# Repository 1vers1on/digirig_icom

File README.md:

# ICOM IC-2730 Digital Controller

A custom hardware controller for the ICOM IC-2730 radio, featuring digital audio processing and USB connectivity.

## Overview

This project provides a digital interface for the ICOM IC-2730 radio using a Raspberry Pi RP2350 microcontroller and TLV320AIC3204 audio codec. It handles both transmit and receive audio digitally while managing the radio's unique logic level requirements.

## Hardware
### Main Components

- **Microcontroller: Raspberry Pi RP2350**
  - High processing power
  - Native USB support
  - Familiar development ecosystem

- **Audio Codec: TLV320AIC3204**
  - Integrated DAC and ADC
  - High-quality audio processing

## Key Features
  - USB connectivity for computer interface
  - Bidirectional audio processing (TX/RX)
  - Analog switching circuitry
  - LDO power regulation
  - 3D-printed enclosure with screw mounting

## Design Challenges
**Logic Level Weirdness**
The ICOM IC-2730 uses some very unusual logic levels that I've never encountered before:

- High: 5V
- Low: 3.1V (yes, really!)

**Solution**

- RX path: LM393 comparator to handle the odd voltage levels
- TX path: 5V level shifter (if it reads 3.1V as low, it should read 0V as low too)

**Power Management**
Originally considered a buck converter for efficiency, but went with an LDO since it's perfectly adequate for this application and simpler to implement.

## Notes

- This was my first time using Fusion 360 for CAD work
- Spent way too long figuring out MOSFET power switching
- Enclosure uses screws instead of glue for user serviceability

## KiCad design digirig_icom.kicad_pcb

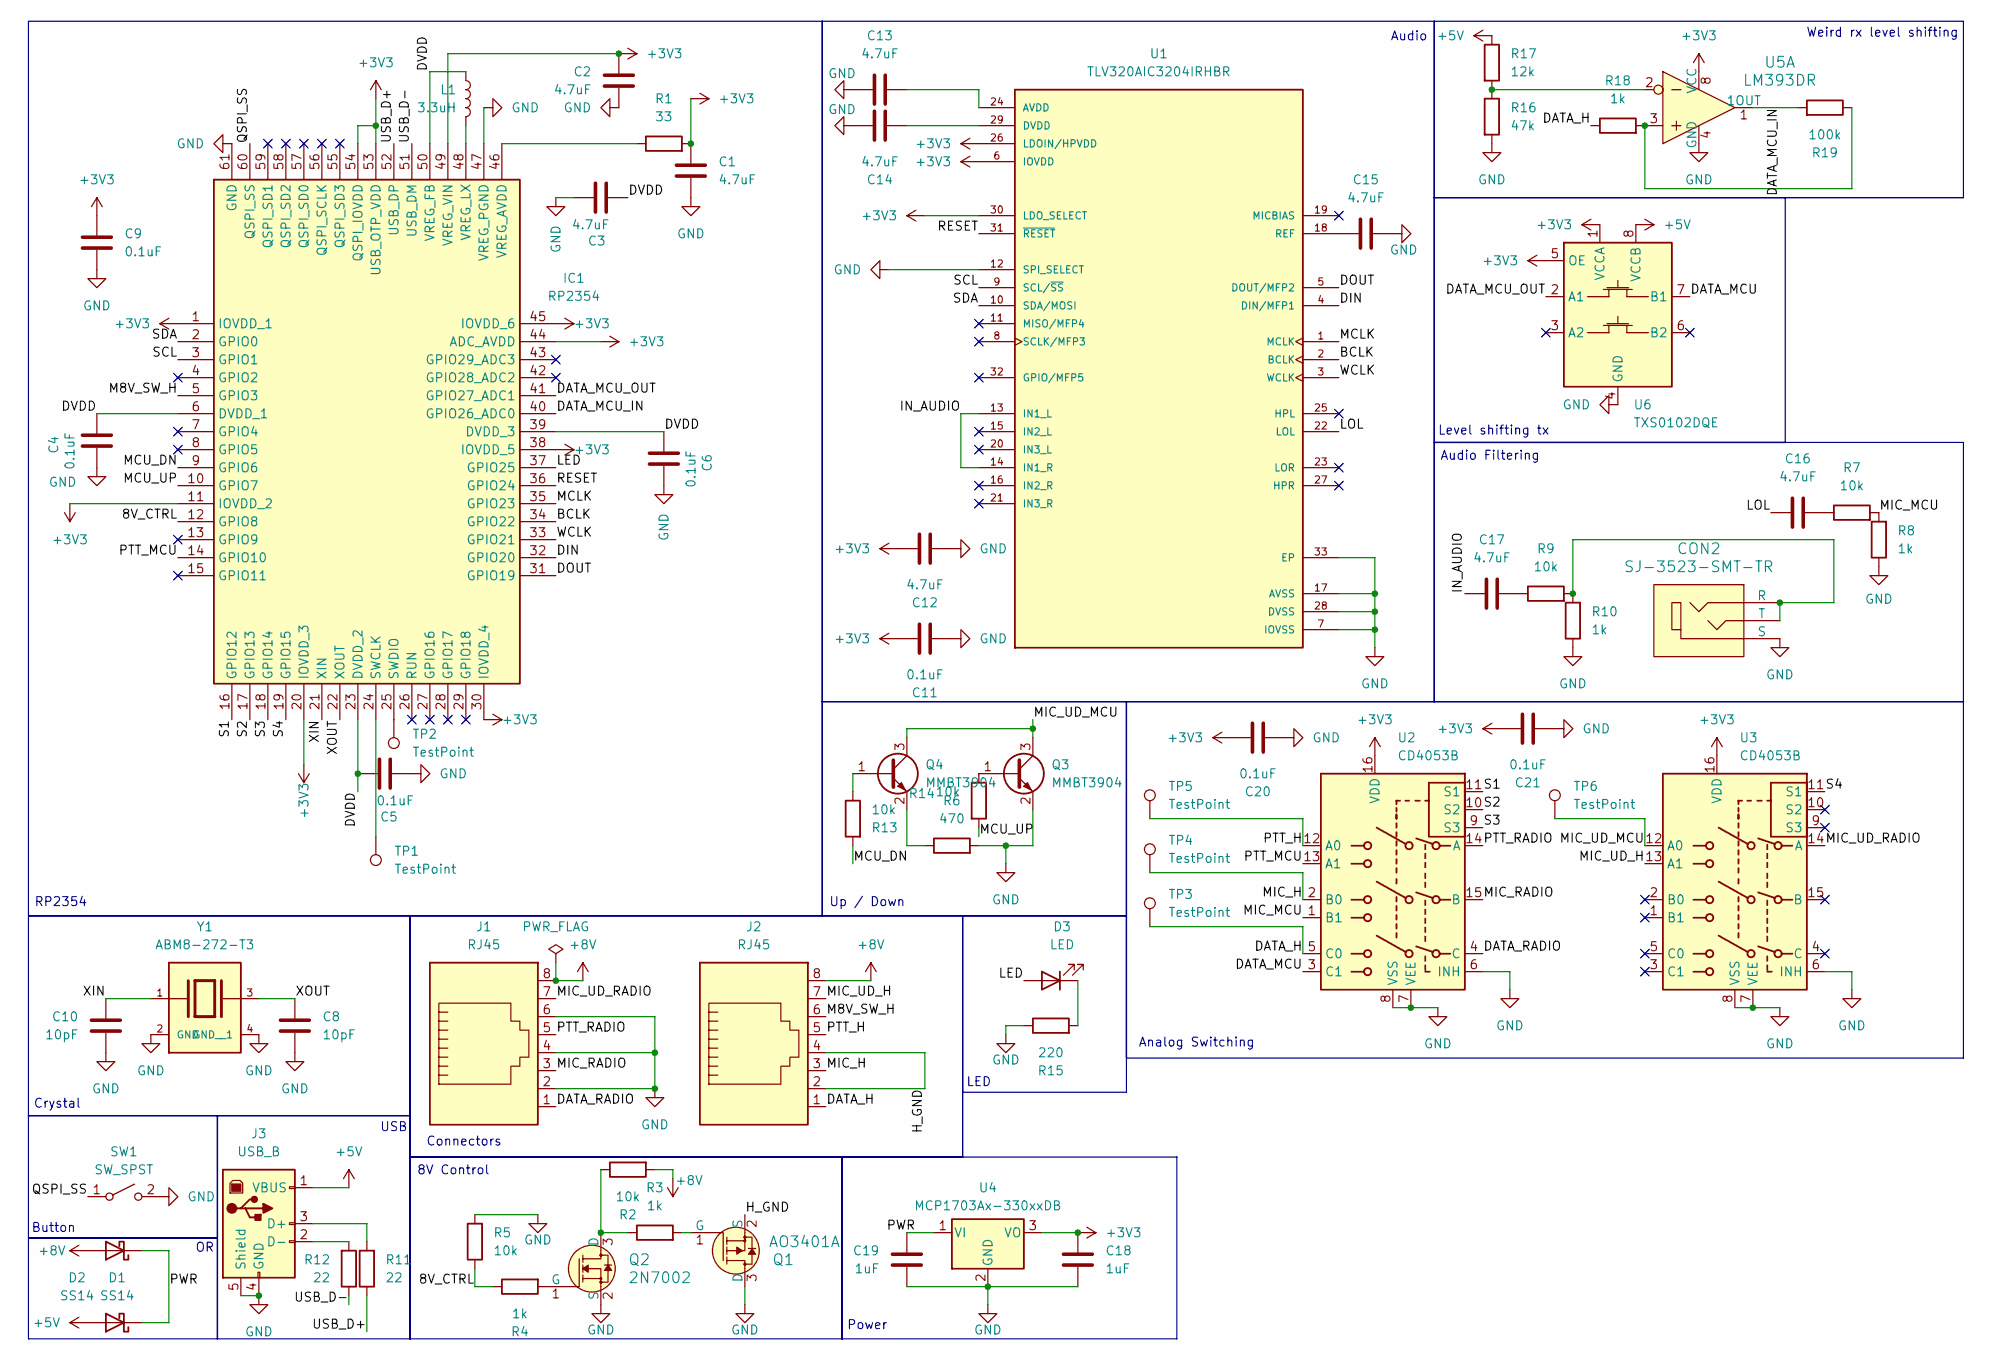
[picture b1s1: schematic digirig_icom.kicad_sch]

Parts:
C1, C2, C3, C12, C13, C14, C15, C16, C17: 4.7uF; C_0402_1005Metric; Digi-Key_PN 1276-1482-2-ND
C4, C5, C6, C9, C11, C20, C21: 0.1uF; C_0402_1005Metric; Digi-Key_PN 1276-1043-2-ND
C8, C10: 10pF; C_0402_1005Metric; Digi-Key_PN 490-6186-2-ND
C18, C19: 1uF; C_0402_1005Metric; Digi-Key_PN 1276-1010-2-ND
CON2: SJ-3523-SMT-TR; Switch_Slide_11.6x4mm_SJ-3523-SMT; MPN SJ-3523-SMT-TR; Digi-Key_PN CP-3523SJCT-ND
D1, D2: SS14; D_SMA; Digi-Key_PN SS14TR-ND
D3: LED; LED_0603_1608Metric; Digi-Key_PN 475-LSQ976-NR-1TR-ND
IC1: RP2354; QFN40P700X700X90-61N-D; Manufacturer_Part_Number RP2350A-CT; Digi-Key_PN 2648-SC1511(13)-A4TR-ND
J1, J2: RJ45; RJ45_Amphenol_54602-x08_Horizontal; Digi-Key_PN 609-1046-ND
J3: USB_B; USB_B_Lumberg_2411_02_Horizontal; Digi-Key_PN 5405-241106-ND
L1: 3.3uH; AOTAB201610S3R3101T; Digi-Key_PN 535-AOTA-B201610S3R3-101-TTR-ND
Q1: AO3401A; SOT-23-3; MPN AO3401A; Digi-Key_PN 785-1001-1-ND
Q2: 2N7002; SOT-23-3; MPN 2N7002; Digi-Key_PN 2N7002NCT-ND
Q3, Q4: MMBT3904; SOT-23; Digi-Key_PN 4878-MMBT3904TR-ND
R1: 33; R_0402_1005Metric; Digi-Key_PN 311-33JRTR-ND
R2, R5, R7, R9, R13, R14: 10k; R_0402_1005Metric; Digi-Key_PN 311-10.0KLRTR-ND
R3, R4, R8, R10, R18: 1k; R_0402_1005Metric; Digi-Key_PN 311-1.0KJRTR-ND
R6: 470; R_0402_1005Metric; Digi-Key_PN 311-470LRTR-ND
R11, R12: 22; R_0402_1005Metric; Digi-Key_PN 311-22.0LRTR-ND
R15: 220; R_0603_1608Metric; Digi-Key_PN 311-220HRTR-ND
R16: 47k; R_0402_1005Metric; Digi-Key_PN 311-47.0KLRTR-ND
R17: 12k; R_0402_1005Metric; Digi-Key_PN P12KDCTR-ND
R19: 100k; R_0402_1005Metric; Digi-Key_PN 311-100KJRTR-ND
SW1: SW_SPST; SW_SPST_CK_RS282G05A3; Digi-Key_PN CKN10384TR-ND
TP1, TP2, TP3, TP4, TP5, TP6: TestPoint; TestPoint_Pad_D1.0mm
U1: TLV320AIC3204IRHBR; QFN50P500X500X100-33N; PARTREV E; Digi-Key_PN 296-23775-2-ND
U2, U3: CD4053B; TSSOP-16_4.4x5mm_P0.65mm; Digi-Key_PN 296-14117-2-ND
U4: MCP1703Ax-330xxDB; SOT-223-3_TabPin2; Digi-Key_PN MCP1703A-3302E/DB-ND
U5: LM393DR; SOIC-8_W3.9mm; MPN LM393DR; Digi-Key_PN 296-1015-1-ND
U6: TXS0102DQE; X2SON-8_1.4x1mm_P0.35mm; Digi-Key_PN 296-28368-2-ND
Y1: ABM8-272-T3; XTAL_ABM8-272-T3; PARTREV 07-29-20; Digi-Key_PN 535-ABM8-272-T3TR-ND

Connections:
+3V3: C1.1, C2.2, C9.2, C11.1, C12.1, C18.1, C20.1, C21.1, IC1.1 (IOVDD_1), IC1.11 (IOVDD_2), IC1.20 (IOVDD_3), IC1.30 (IOVDD_4), IC1.38 (IOVDD_5), IC1.44 (ADC_AVDD), IC1.45 (IOVDD_6), IC1.49 (VREG_VIN), IC1.53 (USB_OTP_VDD), IC1.54 (QSPI_IOVDD), R1.2, U1.6 (IOVDD), U1.26 (LDOIN/HPVDD), U1.30 (LDO_SELECT), U2.16 (VDD), U3.16 (VDD), U4.3 (VO), U5.8 (VCC), U6.1 (VCCA), U6.5 (OE)
+5V: D1.2 (A), J3.1 (VBUS), R17.1, U6.8 (VCCB)
+8V: D2.2 (A), J1.8, J2.8, R2.2
/8V_CTRL: IC1.12 (GPIO8), R4.1, R5.1
/BCLK: IC1.34 (GPIO22), U1.2 (BCLK)
/DATA_H: J2.1, R18.1, TP3.1, U2.5 (C0)
/DATA_MCU: U2.3 (C1), U6.7 (B1)
/DATA_MCU_IN: IC1.40 (GPIO26_ADC0), R19.2, U5.1 (1OUT)
/DATA_MCU_OUT: IC1.41 (GPIO27_ADC1), U6.2 (A1)
/DATA_RADIO: J1.1, U2.4 (C)
/DIN: IC1.32 (GPIO20), U1.4 (DIN/MFP1)
/DOUT: IC1.31 (GPIO19), U1.5 (DOUT/MFP2)
/DVDD: C3.1, C4.1, C5.1, C6.1, IC1.6 (DVDD_1), IC1.23 (DVDD_2), IC1.39 (DVDD_3), IC1.50 (VREG_FB), L1.2
/H_GND: J2.2, J2.4, Q1.2 (S)
/IN_AUDIO: C17.1, U1.13 (IN1_L), U1.14 (IN1_R)
/LED: D3.2 (A), IC1.37 (GPIO25)
/LOL: C16.1, U1.22 (LOL)
/M8V_SW_H: IC1.5 (GPIO3), J2.6
/MCLK: IC1.35 (GPIO23), U1.1 (MCLK)
/MCU_DN: IC1.9 (GPIO6), R13.2
/MCU_UP: IC1.10 (GPIO7), R14.2
/MIC_H: J2.3, TP4.1, U2.2 (B0)
/MIC_MCU: R7.2, R8.2, U2.1 (B1)
/MIC_RADIO: J1.3, U2.15 (B)
/MIC_UD_H: J2.7, U3.13 (A1)
/MIC_UD_MCU: Q3.3 (C), Q4.3 (C), TP6.1, U3.12 (A0)
/MIC_UD_RADIO: J1.7, U3.14 (A)
/PTT_H: J2.5, TP5.1, U2.12 (A0)
/PTT_MCU: IC1.14 (GPIO10), U2.13 (A1)
/PTT_RADIO: J1.5, U2.14 (A)
/PWR: C19.1, D1.1 (K), D2.1 (K), U4.1 (VI)
/QSPI_SS: IC1.60 (QSPI_SS), SW1.1 (A)
/RESET: IC1.36 (GPIO24), U1.31 (~RESET)
/S1: IC1.16 (GPIO12), U2.11 (S1)
/S2: IC1.17 (GPIO13), U2.10 (S2)
/S3: IC1.18 (GPIO14), U2.9 (S3)
/S4: IC1.19 (GPIO15), U3.11 (S1)
/SCL: IC1.3 (GPIO1), U1.9 (SCL/~SS)
/SDA: IC1.2 (GPIO0), U1.10 (SDA/MOSI)
/USB_D+: IC1.52 (USB_DP), R11.1
/USB_D-: IC1.51 (USB_DM), R12.1
/WCLK: IC1.33 (GPIO21), U1.3 (WCLK)
/XIN: C10.1, IC1.21 (XIN), Y1.1
/XOUT: C8.1, IC1.22 (XOUT), Y1.3
GND: C1.2, C2.1, C3.2, C4.2, C5.2, C6.2, C8.2, C9.1, C10.2, C11.2, C12.2, C13.2, C14.1, C15.1, C18.2, C19.2, C20.2, C21.2, CON2.1 (S), IC1.47 (VREG_PGND), IC1.61 (GND), J1.2, J1.4, J1.6, J3.4 (GND), J3.5 (Shield), Q1.3 (D), Q2.2 (S), Q3.2 (E), R5.2, R6.2, R8.1, R10.1, R15.1, R16.2, SW1.2 (B), U1.7 (IOVSS), U1.12 (SPI_SELECT), U1.17 (AVSS), U1.28 (DVSS), U1.33 (EP), U2.6 (INH), U2.7 (VEE), U2.8 (VSS), U3.6 (INH), U3.7 (VEE), U3.8 (VSS), U4.2 (GND), U5.4 (GND), U6.4 (GND), Y1.2 (GND), Y1.4 (GND__1)
unnamed: C16.2, R7.1
unnamed: C17.2, R9.1
unnamed: CON2.2 (T), CON2.3 (R), R9.2, R10.2
unnamed: D3.1 (K), R15.2
unnamed: IC1.24 (SWCLK), TP1.1
unnamed: IC1.25 (SWDIO), TP2.1
unnamed: IC1.46 (VREG_AVDD), R1.1
unnamed: IC1.48 (VREG_LX), L1.1
unnamed: J3.3 (D+), R11.2
unnamed: J3.2 (D-), R12.2
unnamed: Q1.1 (G), R3.2
unnamed: Q2.3 (D), R2.1, R3.1
unnamed: Q2.1 (G), R4.2
unnamed: Q3.1 (B), R14.1
unnamed: Q4.1 (B), R13.1
unnamed: Q4.2 (E), R6.1
unnamed: R16.1, R17.2, U5.2
unnamed: R18.2, R19.1, U5.3
unnamed: C13.1, U1.24 (AVDD)
unnamed: C14.2, U1.29 (DVDD)
unnamed: C15.2, U1.18 (REF)

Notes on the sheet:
Audio Filtering
Up / Down
RP2354
Weird rx level shifting
LED
8V Control
Level shifting tx
Analog Switching
Connectors
Audio
Crystal
Button
Power
USB

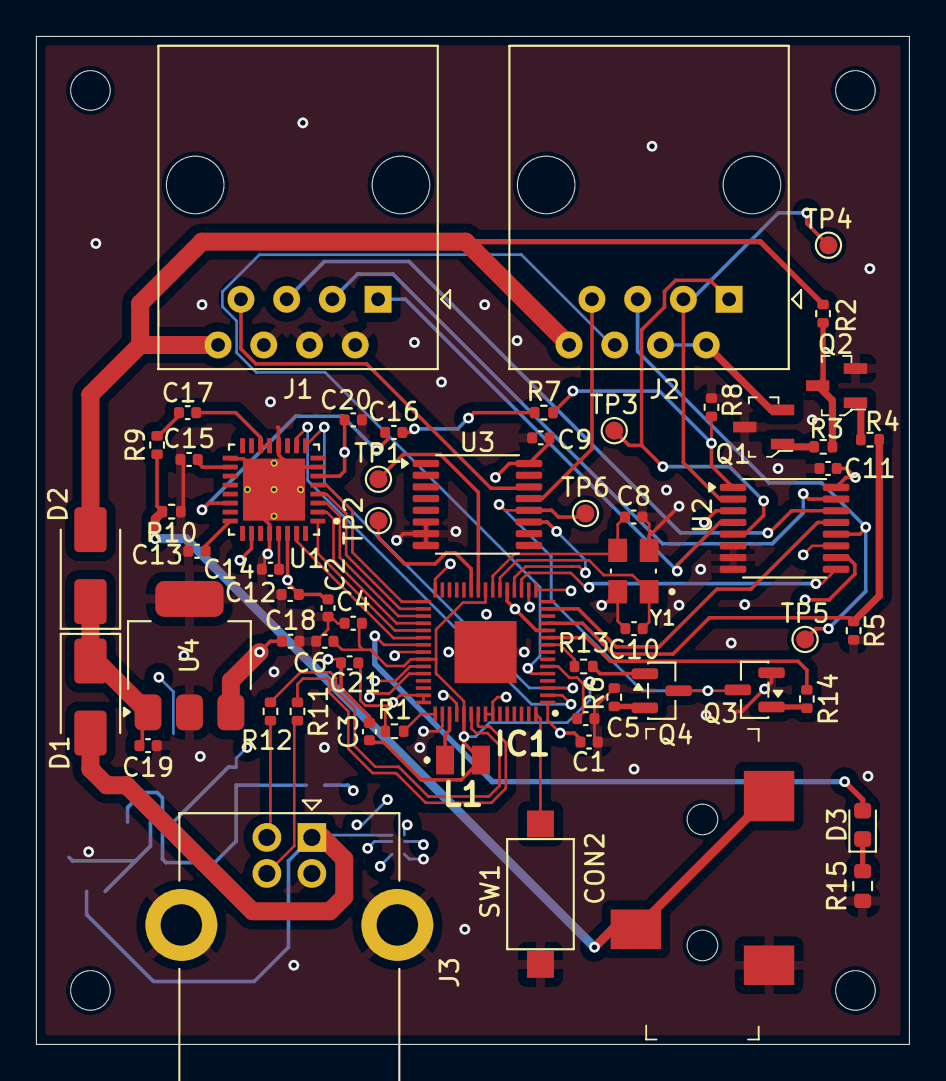
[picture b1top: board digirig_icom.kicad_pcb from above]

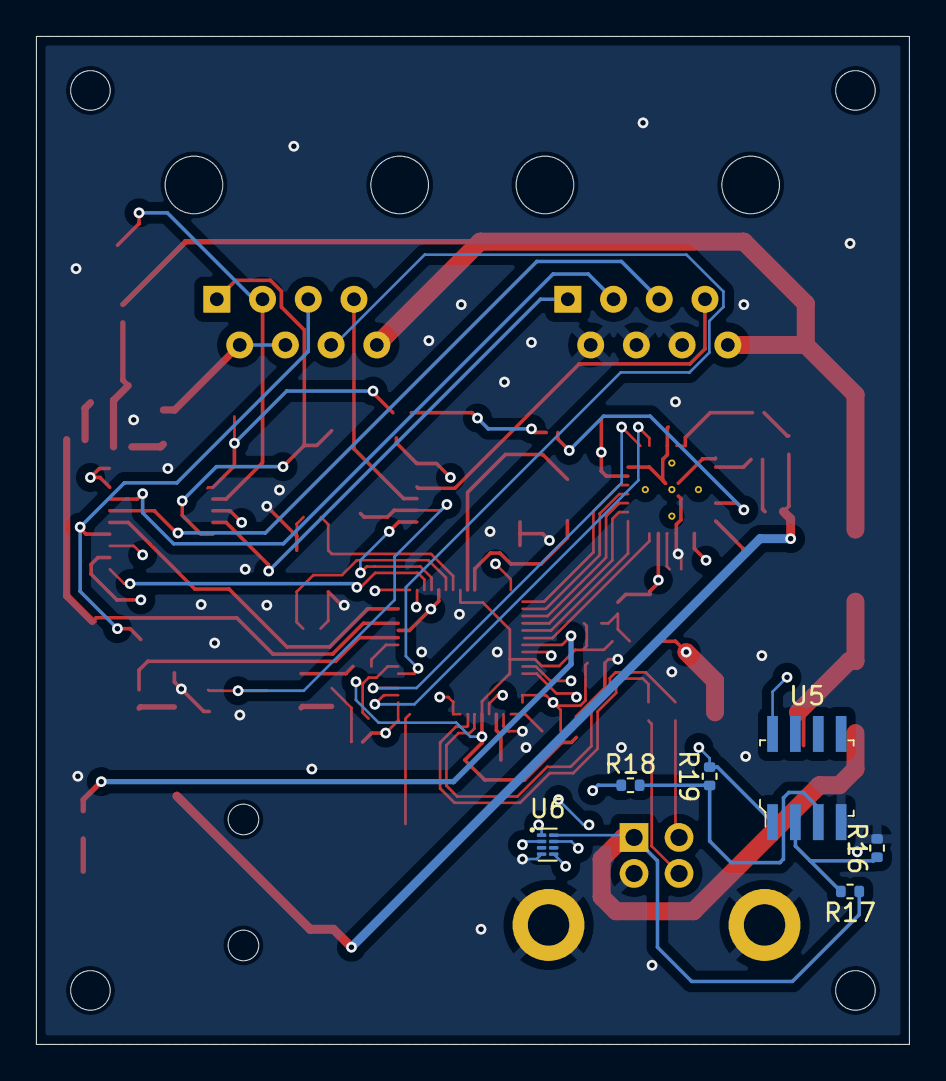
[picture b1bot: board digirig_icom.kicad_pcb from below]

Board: 4 copper layers, 48.5 x 56.0 mm, 66 parts (6 on the bottom side), 66 nets.

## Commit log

2026-01-28 Weird level shifting stuff I think
2026-01-28 remove gerbers
2026-01-28 remove models
2026-01-28 Add 3d models for the case
2026-01-28 Add README.md
2026-01-28 Fix some stuff
